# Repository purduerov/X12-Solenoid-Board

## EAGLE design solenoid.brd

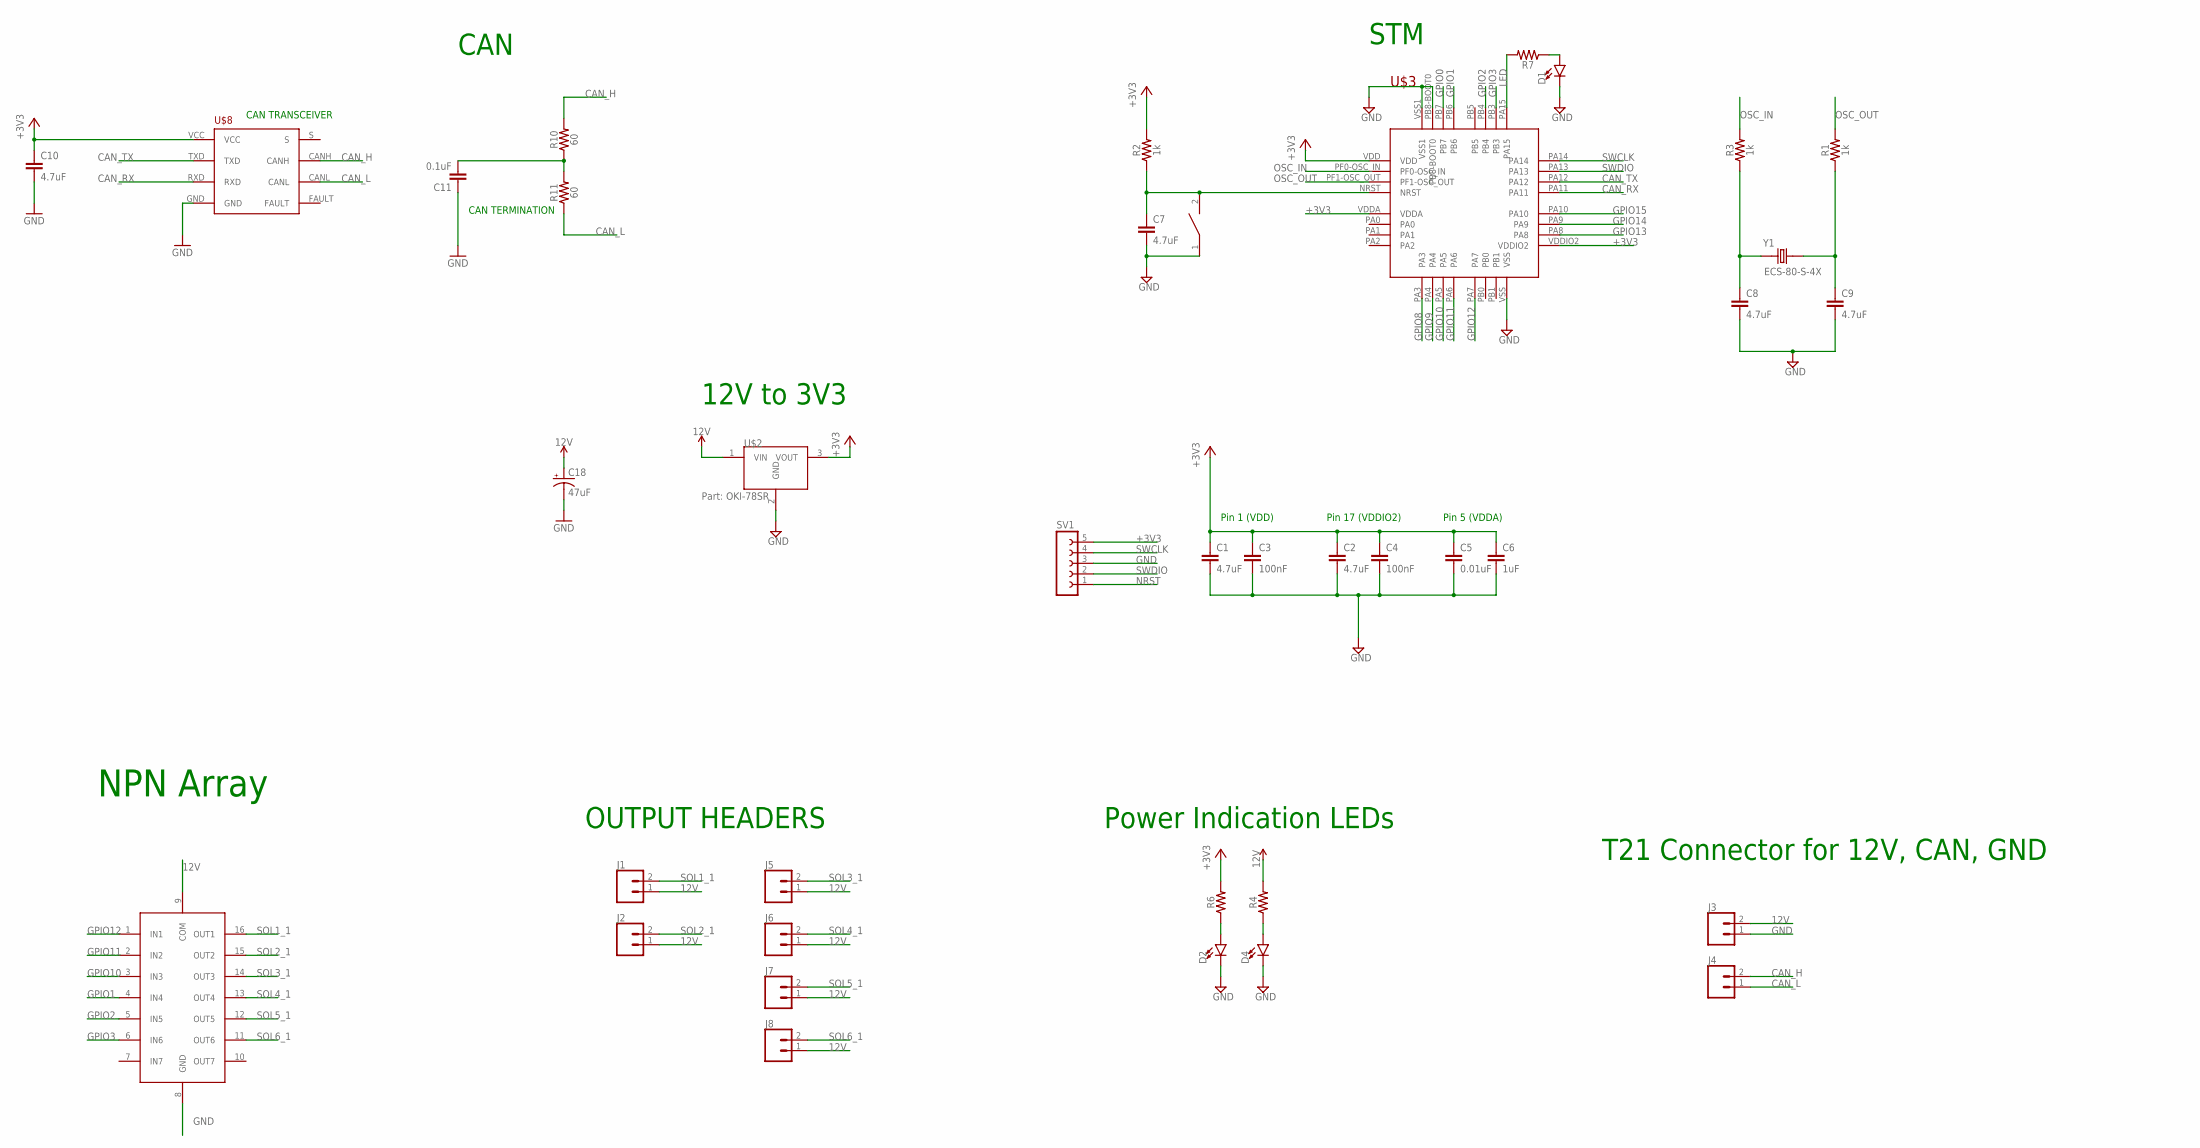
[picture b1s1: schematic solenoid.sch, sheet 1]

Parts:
C1, C2, C7, C8, C9, C10: 4.7uF; 0603
C3, C4: 100nF; 0603
C5: 0.01uF; 0603
C6: 1uF; 0603
C11: 0.1uF; 0603
C18: 47uF; PANASONIC_D
D1, D2, D4: LED0603; LED-0603
J1, J2, J3, J4, J5, J6, J7, J8: CONN_02; 1X02
R1, R2, R3: 1k; 0603
R4, R6, R7: 0603
R10, R11: 60; 0603
RESET: SWITCH; SW_2512
SV1: FE05-1
U1: ULN2003V12
U$2: MURATA-DC-DC
U$3: STM32F042K6T6
U$8: TCAN337D
Y1: ECS-80-S-4X; XTAL_ECS-80-S-4X

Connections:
12V: C18.+, J1.1, J2.1, J3.2, J5.1, J6.1, J7.1, J8.1, R4.2, U1.9 (COM), U$2.1 (VIN)
+3V3: C1.1, C2.1, C3.1, C4.1, C5.1, C6.1, C10.1, R2.2, R6.2, SV1.5, U$2.3 (VOUT), U$3.VDD, U$3.VDDA, U$3.VDDIO2, U$8.VCC
CAN_H: J4.2, R10.2, U$8.CANH
CAN_L: J4.1, R11.1, U$8.CANL
CAN_RX: U$3.PA11, U$8.RXD
CAN_TX: U$3.PA12, U$8.TXD
GND: C1.2, C2.2, C3.2, C4.2, C5.2, C6.2, C7.2, C8.2, C9.2, C10.2, C11.1, C18.-, D1.C, D2.C, D4.C, J3.1, RESET.1, SV1.3, U1.8 (GND), U$2.2 (GND), U$3.PB8-BOOT0, U$3.VSS, U$3.VSS1, U$8.GND
GPIO0: U$3.PB7
GPIO1: U1.4 (IN4), U$3.PB6
GPIO2: U1.5 (IN5), U$3.PB4
GPIO3: U1.6 (IN6), U$3.PB3
GPIO8: U$3.PA3
GPIO9: U$3.PA4
GPIO10: U1.3 (IN3), U$3.PA5
GPIO11: U1.2 (IN2), U$3.PA6
GPIO12: U1.1 (IN1), U$3.PA7
GPIO13: U$3.PA8
GPIO14: U$3.PA9
GPIO15: U$3.PA10
LED: R7.2, U$3.PA15
unnamed: C9.1, R1.1, Y1.2
unnamed: C8.1, R3.1, Y1.1
unnamed: C11.2, R10.1, R11.2
unnamed: D1.A, R7.1
unnamed: D4.A, R4.1
unnamed: D2.A, R6.1
NRST: SV1.1
NRST1: C7.1, R2.1, RESET.2, U$3.NRST
OSC_IN: R3.2, U$3.PF0-OSC_IN
OSC_OUT: R1.2, U$3.PF1-OSC_OUT
SOL1_1: J1.2, U1.16 (OUT1)
SOL2_1: J2.2, U1.15 (OUT2)
SOL3_1: J5.2, U1.14 (OUT3)
SOL4_1: J6.2, U1.13 (OUT4)
SOL5_1: J7.2, U1.12 (OUT5)
SOL6_1: J8.2, U1.11 (OUT6)
SWCLK: SV1.4, U$3.PA14
SWDIO: SV1.2, U$3.PA13

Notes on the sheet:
CAN
OUTPUT HEADERS
Power Indication LEDs
12V to 3V3
CAN TRANSCEIVER
CAN TERMINATION
T21 Connector for 12V, CAN, GND
NPN Array
STM
Pin 1 (VDD)
Pin 17 (VDDIO2)
Pin 5 (VDDA)

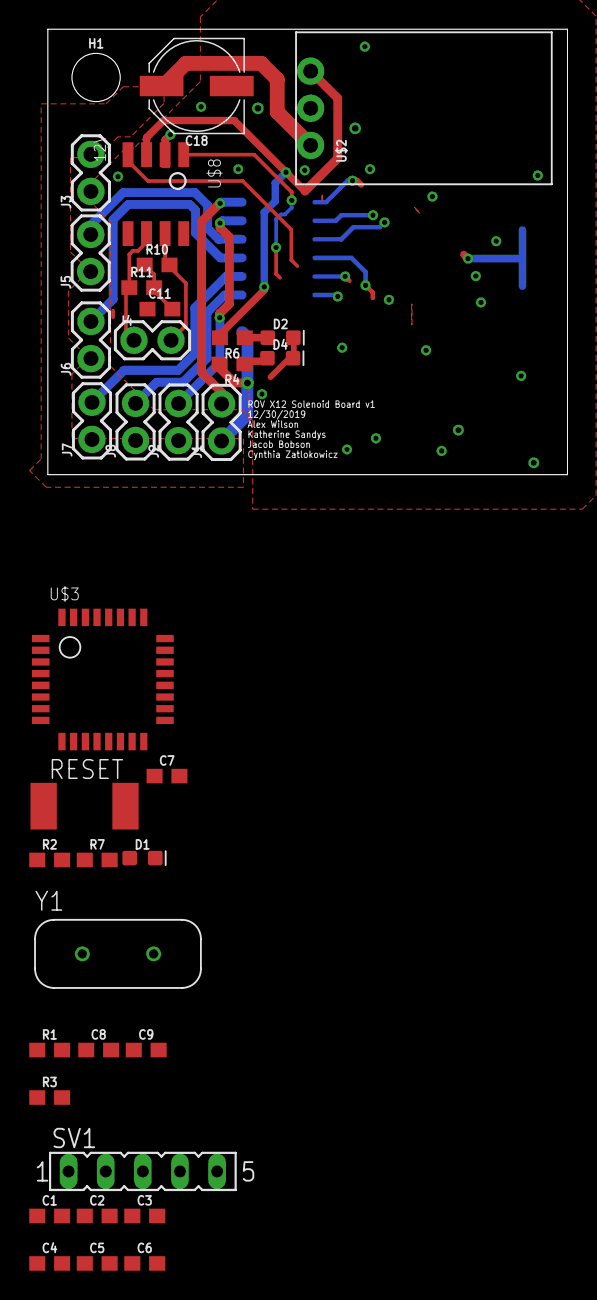
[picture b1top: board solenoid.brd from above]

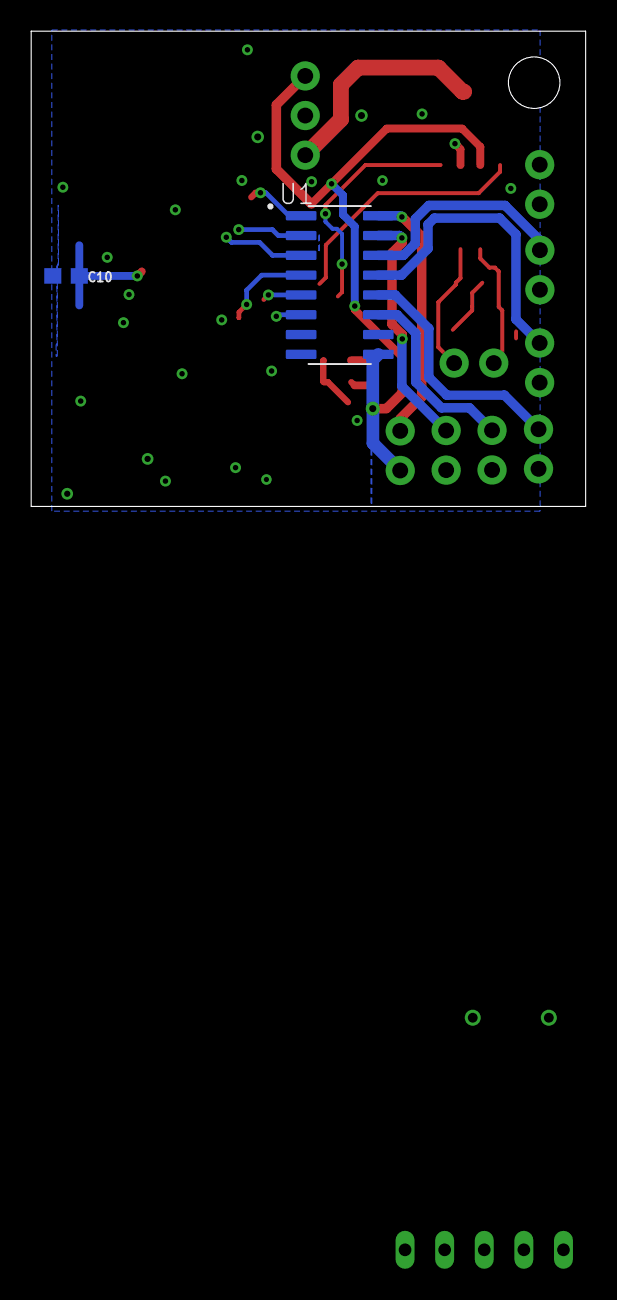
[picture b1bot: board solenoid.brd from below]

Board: 2 copper layers, 35.6 x 30.5 mm, 39 parts (2 on the bottom side), 31 nets.

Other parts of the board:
H1: STAND-OFF

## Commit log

2019-10-09 Created new schematic from last year's
    Created the new schematic based off of components from last year.
    Major components are the CAN and STM block, GPIO mosfets, and 12V to 3V3 converter.
2019-10-16 Switched mosfets out for H-bridges
    Deleted the solenoid mosfets and replaced them with 4 H-bridge parts
2019-10-24 Created the board and placed everything. Started routing
2019-10-30 Newly sized board w/ schematic changes
    This is the first attempt at routing the 1.2" by 1.4" solenoid board with a removed h-bridge and with some questions as to some airwires
2019-10-30 last version of this board
    abandon all hope of this first draft. It passed DRC for default but not the DRC for ECE Senior Design have to scrap this idea :(
2019-11-07 Clearance issues fixed
2019-11-13 added new components
2019-11-13 small updates
    finished making the wire impedances the same for oscillator and programming header, also made minor wire movements
2019-11-16 added standoff, moved around some header
2019-11-16 added a dxf file to the branch
2019-12-19 Solenoid v1
    Final changes to capacitor and few small changes
2019-12-19 put on bmp
2019-12-19 added some silk screen information about board
2019-12-31 Fixed Labeling
2020-09-10 Make the schematic and board consistent Revert "Fixed Labeling"
    This reverts commit 7386091f4d909d3dfabd7faa3d4cd36d2ed047bf.
2020-09-10 Update 12->3.3 converter, make extra layers inactive, fix names
2020-09-10 buck converter cad
2020-09-12 deleted h bridges - broken
2020-09-12 nmos part and datasheet
2020-09-12 potentially finished schematic
2020-09-19 solenoid work
2020-09-30 worked on some trace things and wiring
2020-09-30 next I make solenoid thingies 20 width
2020-10-03 maybe ready ?
2020-10-03 better can in progress
2020-10-07 cans are equal length now yay and no overlap with 12v
2020-10-07 good board 10/10
2020-10-07 stud edit
2020-10-07 nice
2020-10-26 new connectors. another hole. v2
2020-10-26 final touch-ups

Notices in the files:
parts and their libraries:
SparkFun-Capacitors: Licensing: Creative Commons ShareAlike 4.0 International - https://creativecommons.org/licenses/by-sa/4.0
